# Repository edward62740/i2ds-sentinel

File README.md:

# I<sup>2</sup>DS Sentinel

## Overview
This is part of [I<sup>2</sup>DS](https://github.com/edward62740/i2ds). Utilizes tflite-micro person detector model to detect the presence of people, as well as capture photos when requested by other sensors within the network.

## Operation
This device performs a few main functions:
* Uses person detection to detect presence of humans + visualize activity over time
* Takes pictures when intrusion is detected by the internal sensor network and uploads to Firebase storage to be viewed through app

## Hardware
* ESP32-CAM board with 4Mb PSRAM (mounted on 2.54mm sockets above mainboard)
* EFR32FG23 microcontroller for receiving warnings from the I<sup>2</sup>DS sensor network
* VL53L1X ToF sensor
* Array of 10 WS2812-2020 RGB LEDs
* LIS2DH12TR tri-axis accelerometer
* USB bridge and power management circuits

## Design Constraints
In this project, the main constraints were on system memory.
* Maximum statically allocated RAM is 160kB
* Large amounts of dynamically allocated memory, i.e SSL/TLS, frame buffer

The issues were resolved by utilizing the PSRAM to store most of the Firebase-related protocol overheads + tf arena.

In addition, the tflite person detection model was found to run too slowly for any useful real-time inference. 
The [ESP-NN](https://github.com/espressif/esp-nn) kernel optimizations were used to bring down the inference time from ca. 5000ms to ca. 400ms, allowing for a practical implementation of this model in the ESP32.

_The build flags in platformio.ini must be used or the code will not compile with the kernel optimizations._
<br>

The OV2640 camera was not performant upon restart to JPEG mode, often lacking brightness and appearing tinted. This appears to be a known issue (https://github.com/espressif/esp32-camera/issues/314), (https://github.com/espressif/esp32-camera/issues/383) related to the camera AWB. <br>
The workaround used was to wait for min. 150ms after restarting the camera in order to get a vaguely usable frame, then to persist in JPEG mode until it is no longer needed (implemented in commit [#b9b3d20](https://github.com/edward62740/i2ds-sentinel/commit/b9b3d20fc2c7c2deef02794aad9a063e34ca1ace)). <br><br>

<br>
Note: Due to limited IO, io12 was used for UART rx. ESP32 must be configured in efuse to disregard io12 as strapping pin for VDD_SDIO regulator, or it will fail to boot.

## Mobile App

Captured images and other information can be viewed through the same app as the I<sup>2</sup>DS main system as shown in the screen capture below:

## Low-Light Mods
Removing the IR filter from the OV2640 increased low-light performance while not significantly degrading daylight performance (for indoor use only).
The flash LED was replaced with a VCSEL IR illuminator.

## Privacy Concerns
Queueing a request to capture a frame to upload to Firebase can only be triggered by a warning packet from the internal sensor network. The only requests forwarded to the internal sensor network over IP are state change requests. Hence, it should difficult to falsely trigger this device to take a picture in such a way that privacy is compromised, without the attacker first having physical access and/or security key of the sensor network, appropriate sub-GHz transmitting device, and the Firebase access key.

## Integration with I2DS
This device will work with I2DS from commit [#9158914](https://github.com/edward62740/I2DS/commit/91589148e6d0b51ad65f4bae4d2b9b4c82a5fe6a).

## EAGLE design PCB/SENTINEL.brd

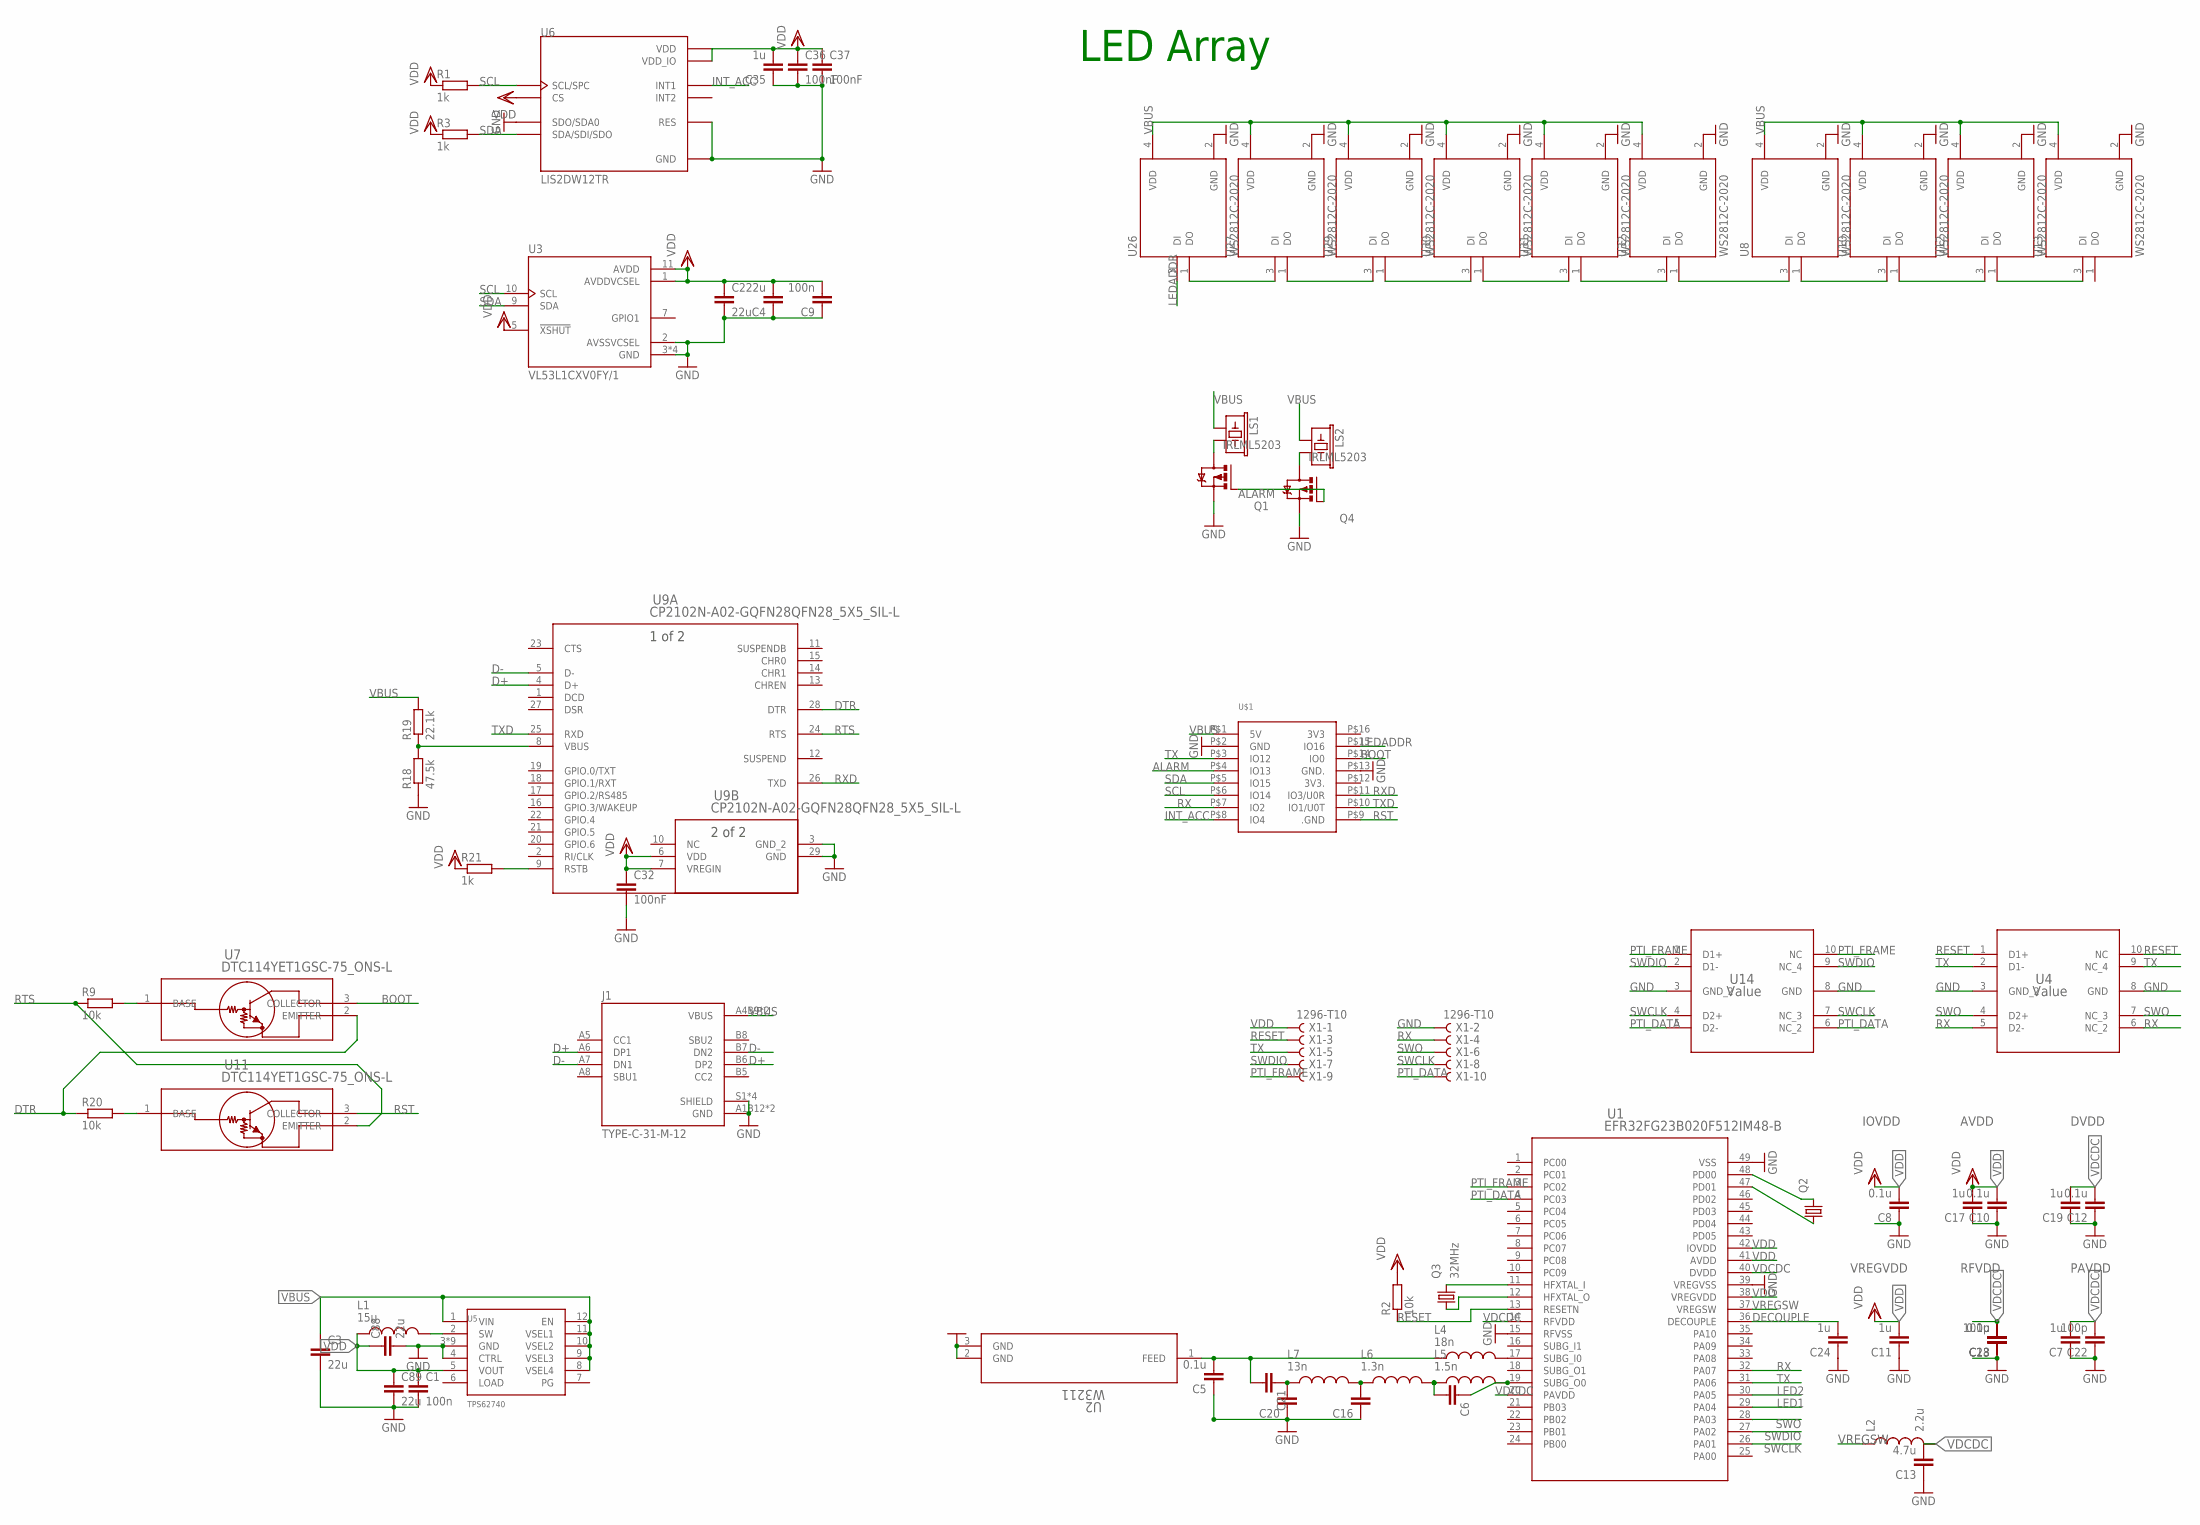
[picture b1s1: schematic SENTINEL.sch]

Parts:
C1, C9: 100n; C0402
C2, C3, C4, C88, C89: 22u; C0603R
C5, C8, C10, C12, C18: 0.1u; C0402
C6: 1.9p; C0402
C7, C11, C17, C19, C24: 1u; C0402
C13: 4.7u; C0603R
C16: 7.2p; C0402
C20: 1.3p; C0402
C21: 220p; C0402
C22, C23: 100p; C0402
C32, C36, C37: 100nF; C0402
C35: 1u; C0603R
J1: TYPE-C-31-M-12; HRO_TYPE-C-31-M-12
L1: 15u; INDC3225X120N
L2: 2.2u; L0603
L4: 18n; INDC0402X26N
L5: 1.5n; INDC0402X26N
L6: 1.3n; INDC0402X26N
L7: 13n; INDC0402X26N
LS1, LS2: BUZZER-PTH_KIT; BUZZER-12MM-KIT
Q1, Q4: IRLML5203; MICRO3
Q2: KX-327-RT; 2.0X1.2
Q3: 32MHz; 2.0X1.6_KX-5
R1, R3, R21: 1k; R0402
R2, R9, R20: 10k; R0402
R18: 47.5k; R0402
R19: 22.1k; R0402
U1: EFR32FG23B020F512IM48-B; QFN_48_SIL
U2: W3211; CHIP_3211_PUL
U3: VL53L1CXV0FY/1; SENSOR_VL53L1CXV0FY/1
U4, U14: Value; DQA0010A
U5: TPS62740; DSS
U6: LIS2DW12TR; LGA12R50P4X4_200X200X70
U7, U11: DTC114YET1GSC-75_ONS-L; SC-75_ONS-L
U8, U10, U12, U13, U26, U27, U29, U30, U31, U32: WS2812C-2020; LED_WS2812C-2020
U9: CP2102N-A02-GQFN28QFN28_5X5_SIL-L; QFN28_5X5_SIL-L
U$1: ESP32-CAM
X1: 1296-T10; 1296-10

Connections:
ALARM: Q1.1 (G), Q4.1 (G), U$1.P$4 (IO13)
BOOT: U7.3 (COLLECTOR), U$1.P$14 (IO0)
D+: J1.A6 (DP1), J1.B6 (DP2), U9.4 (D+)
D-: J1.A7 (DN1), J1.B7 (DN2), U9.5 (D-)
DECOUPLE: C24.2, U1.36 (DECOUPLE)
DTR: R20.1, U7.2 (EMITTER), U9.28 (DTR)
GND: C1.2, C2.2, C3.2, C4.1, C5.1, C7.1, C8.1, C9.1, C10.1, C11.1, C12.1, C13.1, C16.1, C17.1, C18.1, C19.1, C20.1, C22.1, C23.1, C24.1, C32.2, C35.1, C36.2, C37.2, C88.2, C89.2, J1.A1B12 (GND), J1.B1A12 (GND), J1.S1 (SHIELD), J1.S2 (SHIELD), J1.S3 (SHIELD), J1.S4 (SHIELD), Q1.2 (S), Q4.2 (S), R18.1, U1.15 (RFVSS), U1.39 (VREGVSS), U1.49 (VSS), U2.2 (GND), U2.3 (GND), U3.2 (AVSSVCSEL), U3.3 (GND), U3.4 (GND), U3.6 (GND), U3.12 (GND), U4.3 (GND_2), U4.8 (GND), U5.3 (GND), U5.4 (CTRL), U5.13 (GND), U5.14 (GND), U5.15 (GND), U5.16 (GND), U5.18 (GND), U5.19 (GND), U5.20 (GND), U5.P$18 (GND), U6.3 (SDO/SDA0), U6.6 (GND), U6.7 (RES), U6.8 (GND), U8.2 (GND), U9.3 (GND_2), U9.29 (GND), U10.2 (GND), U12.2 (GND), U13.2 (GND), U14.3 (GND_2), U14.8 (GND), U26.2 (GND), U27.2 (GND), U29.2 (GND), U30.2 (GND), U31.2 (GND), U32.2 (GND), U$1.P$2 (GND), U$1.P$13 (GND.), X1.2
INT_ACC: U6.12 (INT1), U$1.P$8 (IO4)
LED1: U1.29 (PA04)
LED2: U1.30 (PA05)
LEDADDR: U26.3 (DI), U$1.P$15 (IO16)
unnamed: LS1.- (2), Q1.3 (D)
unnamed: LS2.- (2), Q4.3 (D)
unnamed: U8.1 (DO), U10.3 (DI)
unnamed: U10.1 (DO), U12.3 (DI)
unnamed: C5.2, C21.2, L4.1, U2.1 (FEED)
unnamed: C6.1, L5.2, U1.19 (SUBG_O0)
unnamed: U12.1 (DO), U13.3 (DI)
unnamed: U8.3 (DI), U32.1 (DO)
unnamed: L1.2, U5.2 (SW)
unnamed: R18.2, R19.1, U9.8 (VBUS)
unnamed: R21.2, U9.9 (RSTB)
unnamed: Q3.3 (2), U1.11 (HFXTAL_I)
unnamed: Q3.1, U1.12 (HFXTAL_O)
unnamed: Q2.1, U1.47 (PD01)
unnamed: Q2.2, U1.48 (PD00)
unnamed: L4.2, U1.17 (SUBG_I0)
unnamed: C6.2, L5.1, L6.2
unnamed: C16.2, L6.1, L7.2
unnamed: C20.2, C21.1, L7.1
unnamed: R20.2, U11.1 (BASE)
unnamed: R9.2, U7.1 (BASE)
unnamed: U26.1 (DO), U27.3 (DI)
unnamed: U27.1 (DO), U29.3 (DI)
unnamed: U29.1 (DO), U30.3 (DI)
unnamed: U30.1 (DO), U31.3 (DI)
unnamed: U31.1 (DO), U32.3 (DI)
PTI_DATA: U1.4 (PC03), U14.5 (D2-), U14.6 (NC_2), X1.10
PTI_FRAME: U1.3 (PC02), U14.1 (D1+), U14.10 (NC), X1.9
RESET: R2.1, U1.13 (RESETN), U4.1 (D1+), U4.10 (NC), X1.3
RST: U11.3 (COLLECTOR), U$1.P$9 (.GND)
RTS: R9.1, U9.24 (RTS), U11.2 (EMITTER)
RX: U1.32 (PA07), U4.5 (D2-), U4.6 (NC_2), U$1.P$7 (IO2), X1.4
RXD: U9.26 (TXD), U$1.P$11 (IO3/U0R)
SCL: R1.2, U3.10 (SCL), U6.1 (SCL/SPC), U$1.P$6 (IO14)
SDA: R3.2, U3.9 (SDA), U6.4 (SDA/SDI/SDO), U$1.P$5 (IO15)
SWCLK: U1.26 (PA01), U14.4 (D2+), U14.7 (NC_3), X1.8
SWDIO: U1.27 (PA02), U14.2 (D1-), U14.9 (NC_4), X1.7
SWO: U1.28 (PA03), U4.4 (D2+), U4.7 (NC_3), X1.6
TX: U1.31 (PA06), U4.2 (D1-), U4.9 (NC_4), U$1.P$3 (IO12), X1.5
TXD: U9.25 (RXD), U$1.P$10 (IO1/U0T)
VBUS: C3.1, J1.A4B9 (VBUS), J1.B4A9 (VBUS), LS1.+ (1), LS2.+ (1), R19.2, U5.1 (VIN), U5.8 (VSEL4), U5.9 (VSEL3), U5.10 (VSEL2), U5.11 (VSEL1), U5.12 (EN), U8.4 (VDD), U10.4 (VDD), U12.4 (VDD), U13.4 (VDD), U26.4 (VDD), U27.4 (VDD), U29.4 (VDD), U30.4 (VDD), U31.4 (VDD), U32.4 (VDD), U$1.P$1 (5V)
VDCDC: C7.2, C12.2, C13.2, C18.2, C19.2, C22.2, C23.2, L2.2, U1.14 (RFVDD), U1.20 (PAVDD), U1.40 (DVDD)
VDD: C1.1, C2.1, C4.2, C8.2, C9.2, C10.2, C11.2, C17.2, C32.1, C35.2, C36.1, C37.1, C88.1, C89.1, L1.1, R1.1, R2.2, R3.1, R21.1, U1.38 (VREGVDD), U1.41 (AVDD), U1.42 (IOVDD), U3.1 (AVDDVCSEL), U3.5 (!XSHUT), U3.11 (AVDD), U5.5 (VOUT), U6.2 (CS), U6.9 (VDD), U6.10 (VDD_IO), U9.6 (VDD), U9.7 (VREGIN), X1.1
VREGSW: L2.1, U1.37 (VREGSW)

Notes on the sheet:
IOVDD
AVDD
DVDD
VREGVDD
RFVDD
PAVDD
LED Array

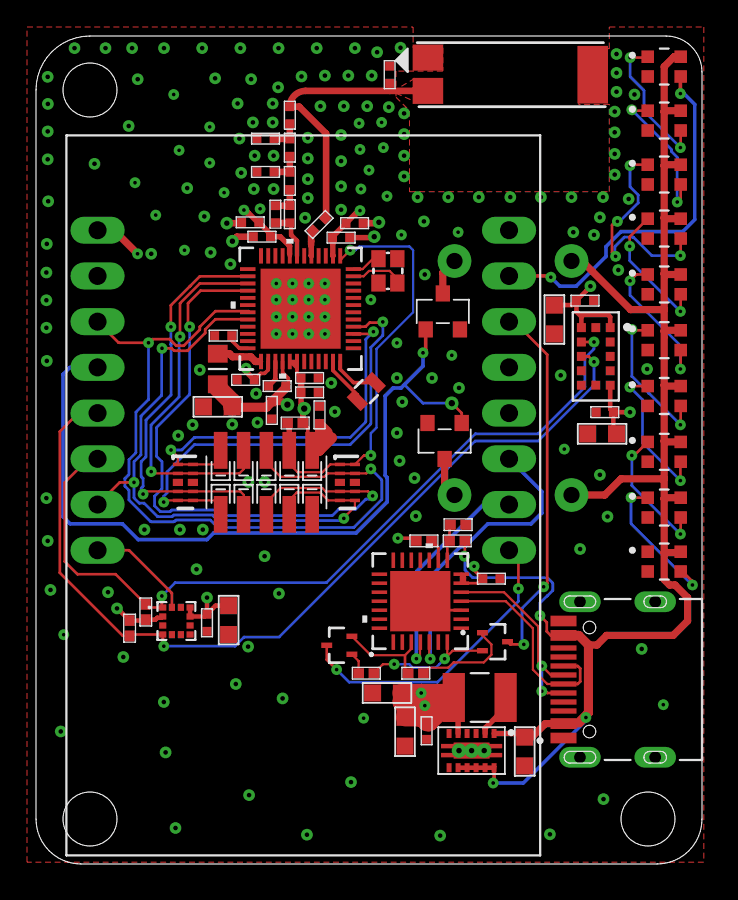
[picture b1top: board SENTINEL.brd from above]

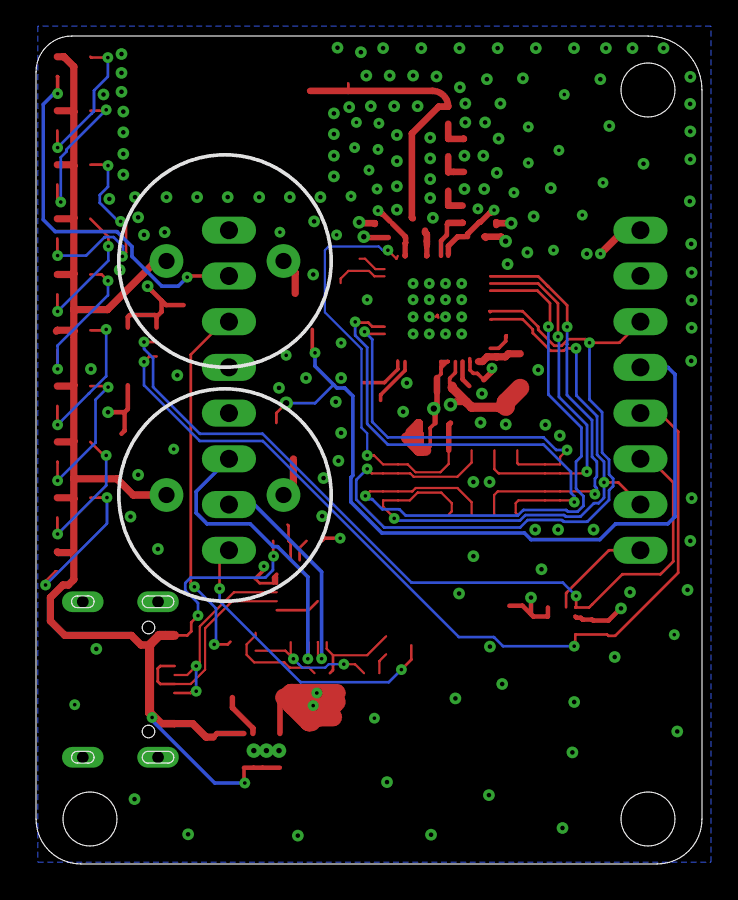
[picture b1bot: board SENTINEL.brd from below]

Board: 4 copper layers, 37.0 x 46.0 mm, 71 parts (2 on the bottom side), 53 nets.

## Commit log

2022-06-04 Initial
2022-06-09 fixed camera issues
2022-06-16 updated detector
2022-06-22 Updated tflite micro to latest and added ESP-NN optimizations
2022-07-22 v1.0 pre-release
2022-07-22 Update documentation and merge efr code
2022-07-22 Create license
2022-07-22 Updated file structure, added PCB files
2022-07-23 Improved queue mechanism
2022-07-24 Added app info
2022-08-04 Added enclosure stl
2022-08-13 Added detector visualization and bug fixes
2022-09-23 Added night vision and VCSEL changes

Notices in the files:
parts and their libraries:
crystal-geyer_V1_0: Copyright: Geyer-Electronic
SparkFun-Electromechanical: Licensing: Creative Commons ShareAlike 4.0 International - https://creativecommons.org/licenses/by-sa/4.0
COPYRIGHT: Copyright (C) 2022 Ultra Librarian. All rights reserved.
